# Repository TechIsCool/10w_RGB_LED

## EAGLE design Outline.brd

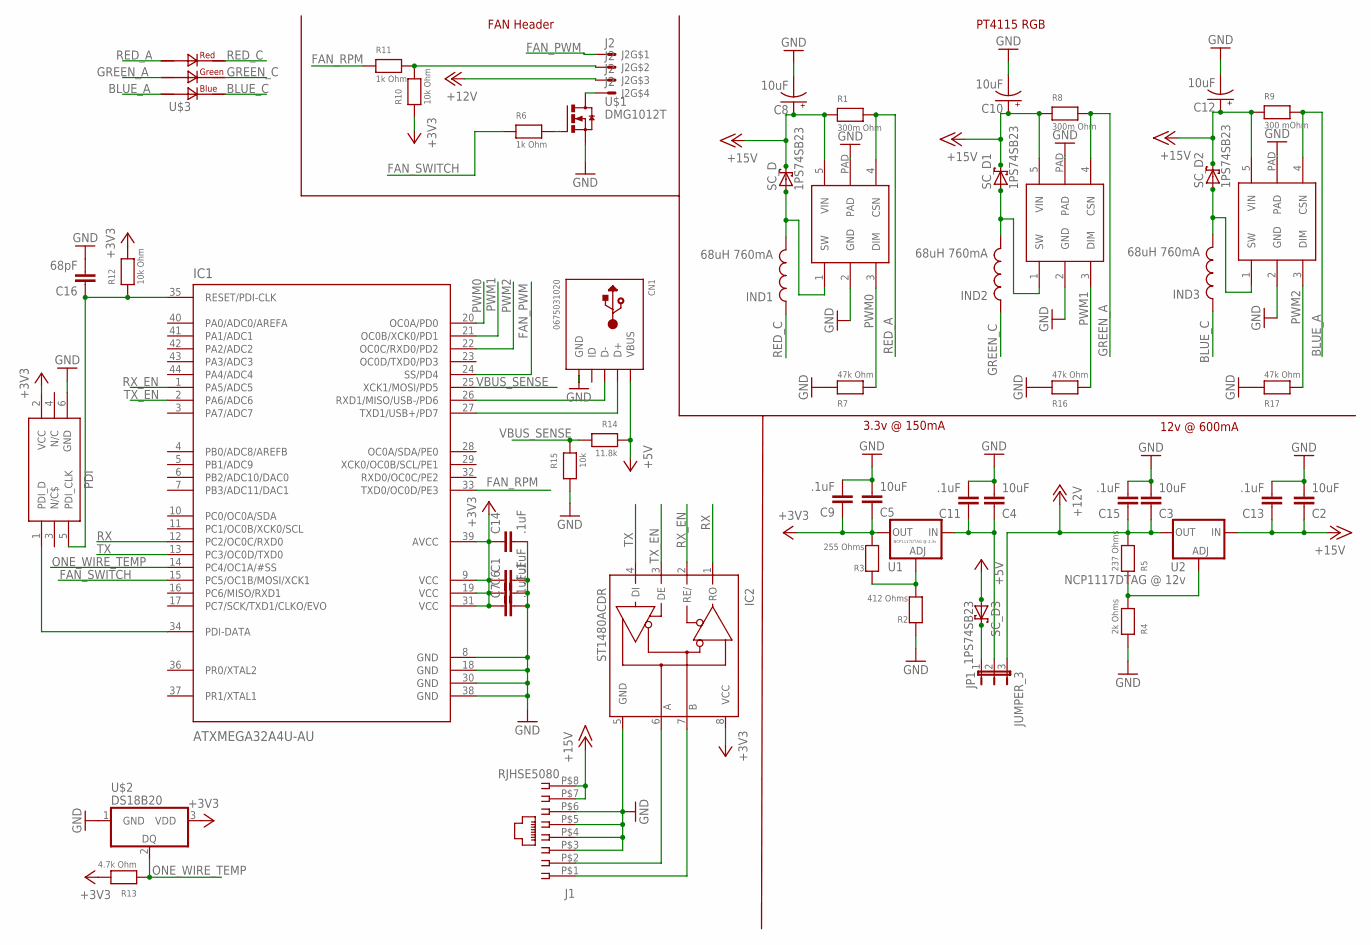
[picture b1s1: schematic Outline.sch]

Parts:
C1, C6, C7, C9, C11, C13, C14, C15: .1uF; 0603-CAP
C2, C3, C4, C5: 10uF; 1210
C8, C10, C12: 10uF; PANASONIC_C
C16: 68pF; 0603-CAP
CN1: 0675031020; MOLEX_675031020
DRV0, DRV1, DRV2: PT4115; SOT89-5
IC1: ATXMEGA32A4U-AU; TQFP-44
IC2: ST1480ACDR; SO08
IND1, IND2, IND3: 68uH 760mA; CR54
J1: RJHSE5080
J2: J2; 47053-1000
JP1: JUMPER_3; JP2E
PDI: AVR_PDI
R1, R8: 300m Ohm; 0805
R2: 412 Ohms; 0603
R3: 255 Ohms; 0603
R4: 2k Ohms; 0603
R5: 237 Ohms; 0603
R6, R11: 1k Ohm; 0603
R7, R16, R17: 47k Ohm; 0603
R9: 300 mOhm; 0805
R10, R12: 10k Ohm; 0603
R13: 4.7k Ohm; 0603
R14: 11.8k; 0603
R15: 10k; 0603
SC_D, SC_D1, SC_D2: 1PS74SB23; SOT-457
SC_D3: 1PS74SB23; NSR05F20
U1: NCP1117DTAG @ 3.3v; V-REG_DPACK
U2: NCP1117DTAG @ 12v; V-REG_DPACK
U$1: DMG1012T
U$2: DS18B20; TOP-92-INLINE
U$3: 10W_RGB_LED; 10W_LED

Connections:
+3V3: C1.1, C5.1, C6.1, C7.1, C9.1, C14.1, IC1.9 (VCC), IC1.19 (VCC), IC1.31 (VCC), IC1.39 (AVCC), IC2.8 (VCC), PDI.2 (VCC), R3.2, R10.1, R12.2, R13.2, U1.4 (OUT), U$2.3 (VDD)
+5V: CN1.P$1 (VBUS), R14.1, SC_D3.P$2 (A)
+12V: C3.1, C15.1, J2.3, JP1.3, R5.2, U2.4 (OUT)
+15V: C2.1, C8.+, C10.+, C12.+, C13.1, DRV0.5 (VIN), DRV1.5 (VIN), DRV2.5 (VIN), J1.P$7 (7), J1.P$8 (8), R1.1, R8.1, R9.1, SC_D.P$2 (C), SC_D.P$5 (C), SC_D1.P$2 (C), SC_D1.P$5 (C), SC_D2.P$2 (C), SC_D2.P$5 (C), U2.3 (IN)
BLUE_A: DRV2.4 (CSN), R9.2, U$3.B$A
BLUE_C: IND3.P$1 (1), U$3.B$C
FAN_PWM: IC1.24 (SS/PD4), J2.1
FAN_RPM: IC1.33 (TXD0/OC0D/PE3), R11.1
FAN_SWITCH: IC1.15 (PC5/OC1B/MOSI/XCK1), R6.1
GND: C1.2, C2.2, C3.2, C4.2, C5.2, C6.2, C7.2, C8.-, C9.2, C10.-, C11.2, C12.-, C13.2, C14.2, C15.2, C16.2, CN1.GND@1 (GND), CN1.GND@2 (GND), CN1.GND@3 (GND), CN1.GND@4 (GND), CN1.P$5 (GND), DRV0.2 (GND), DRV0.PAD, DRV1.2 (GND), DRV1.PAD, DRV2.2 (GND), DRV2.PAD, IC1.8 (GND), IC1.18 (GND), IC1.30 (GND), IC1.38 (GND), IC2.5 (GND), J1.P$3 (3), J1.P$4 (4), J1.P$5 (5), J1.P$6 (6), PDI.6 (GND), R2.1, R4.1, R7.1, R15.2, R16.1, R17.1, U$1.P$S (S), U$2.1 (GND)
GREEN_A: DRV1.4 (CSN), R8.2, U$3.G$A
GREEN_C: IND2.P$1 (1), U$3.G$C
unnamed: R2.2, R3.1, U1.1 (ADJ)
unnamed: R4.2, R5.1, U2.1 (ADJ)
unnamed: J2.4, U$1.P$D (D)
unnamed: R6.2, U$1.P$G (G)
unnamed: JP1.1, SC_D3.P$1 (C)
unnamed: DRV0.1 (SW), IND1.P$2 (2), SC_D.P$1 (A), SC_D.P$3 (A), SC_D.P$4 (A), SC_D.P$6 (A)
unnamed: DRV1.1 (SW), IND2.P$2 (2), SC_D1.P$1 (A), SC_D1.P$3 (A), SC_D1.P$4 (A), SC_D1.P$6 (A)
unnamed: DRV2.1 (SW), IND3.P$2 (2), SC_D2.P$1 (A), SC_D2.P$3 (A), SC_D2.P$4 (A), SC_D2.P$6 (A)
unnamed: IC1.34 (PDI-DATA), PDI.1 (PDI_D)
unnamed: C4.1, C11.1, JP1.2, U1.3 (IN)
unnamed: C16.1, IC1.35 (RESET/PDI-CLK), PDI.5 (PDI_CLK), R12.1
unnamed: J2.2, R10.2, R11.2
ONE_WIRE_TEMP: IC1.14 (PC4/OC1A/#SS), R13.1, U$2.2 (DQ)
PWM0: DRV0.3 (DIM), IC1.20 (OC0A/PD0), R7.2
PWM1: DRV1.3 (DIM), IC1.21 (OC0B/XCK0/PD1), R16.2
PWM2: DRV2.3 (DIM), IC1.22 (OC0C/RXD0/PD2), R17.2
RED_A: DRV0.4 (CSN), R1.2, U$3.R$A
RED_C: IND1.P$1 (1), U$3.R$C
RS485_N: IC2.7 (B), J1.P$1 (1)
RS485_P: IC2.6 (A), J1.P$2 (2)
RX: IC1.12 (PC2/OC0C/RXD0), IC2.1 (RO)
RX_EN: IC1.1 (PA5/ADC5), IC2.2 (RE/)
TX: IC1.13 (PC3/OC0D/TXD0), IC2.4 (DI)
TX_EN: IC1.2 (PA6/ADC6), IC2.3 (DE)
USB+: CN1.P$3 (D+), IC1.27 (TXD1/USB+/PD7)
USB-: CN1.P$2 (D-), IC1.26 (RXD1/MISO/USB-/PD6)
VBUS_SENSE: IC1.25 (XCK1/MOSI/PD5), R14.2, R15.1

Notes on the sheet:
3.3v @ 150mA
12v @ 600mA
PT4115 RGB
FAN Header

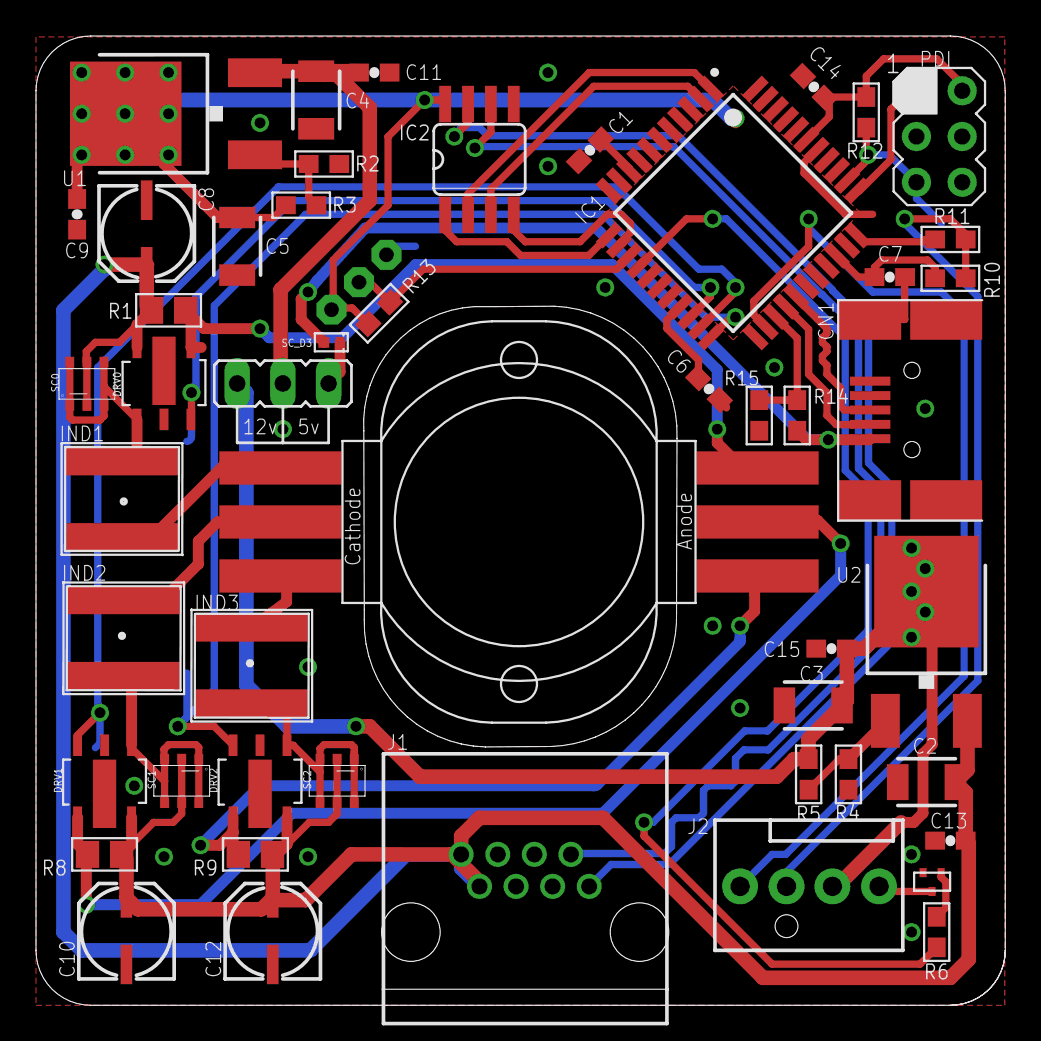
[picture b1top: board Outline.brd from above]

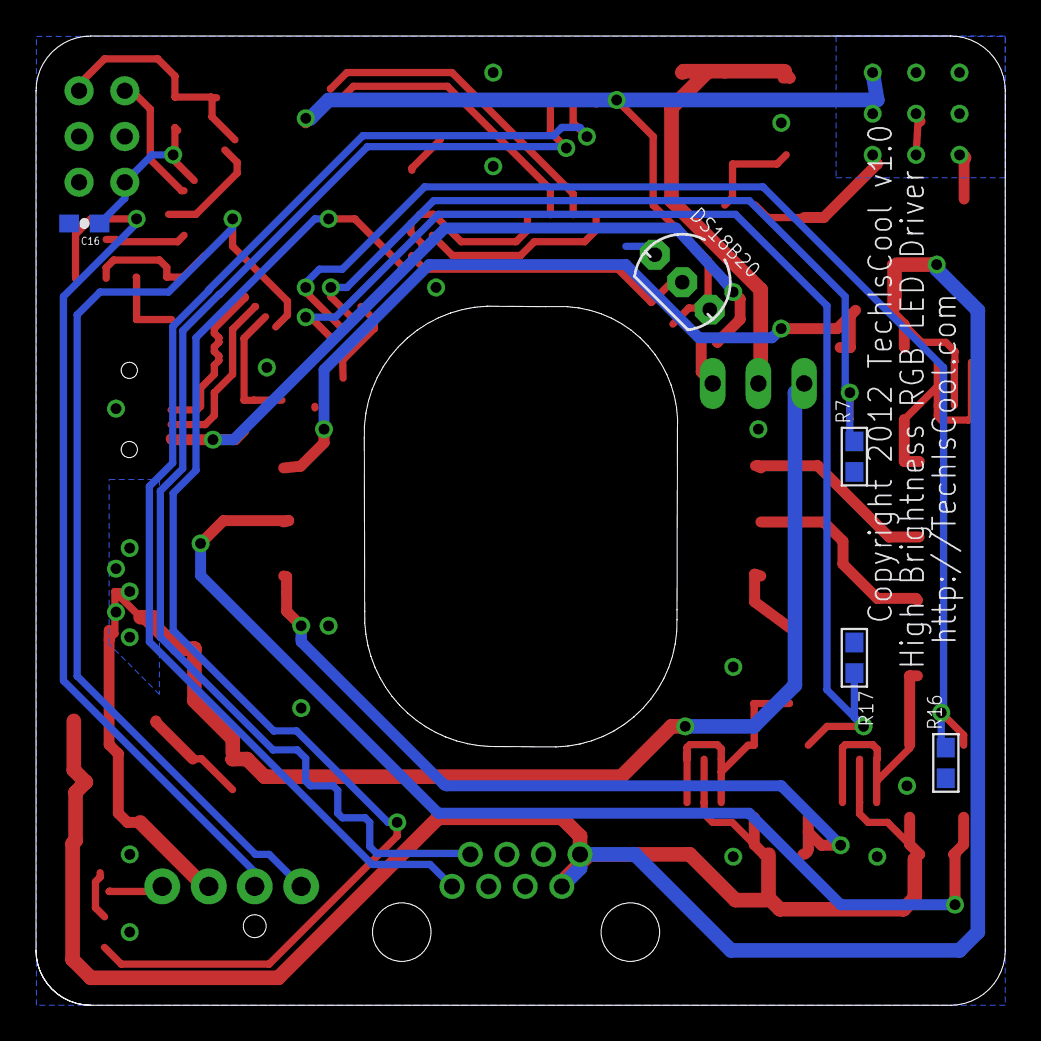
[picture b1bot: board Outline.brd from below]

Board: 2 copper layers, 53.8 x 53.8 mm, 55 parts (5 on the bottom side), 39 nets.

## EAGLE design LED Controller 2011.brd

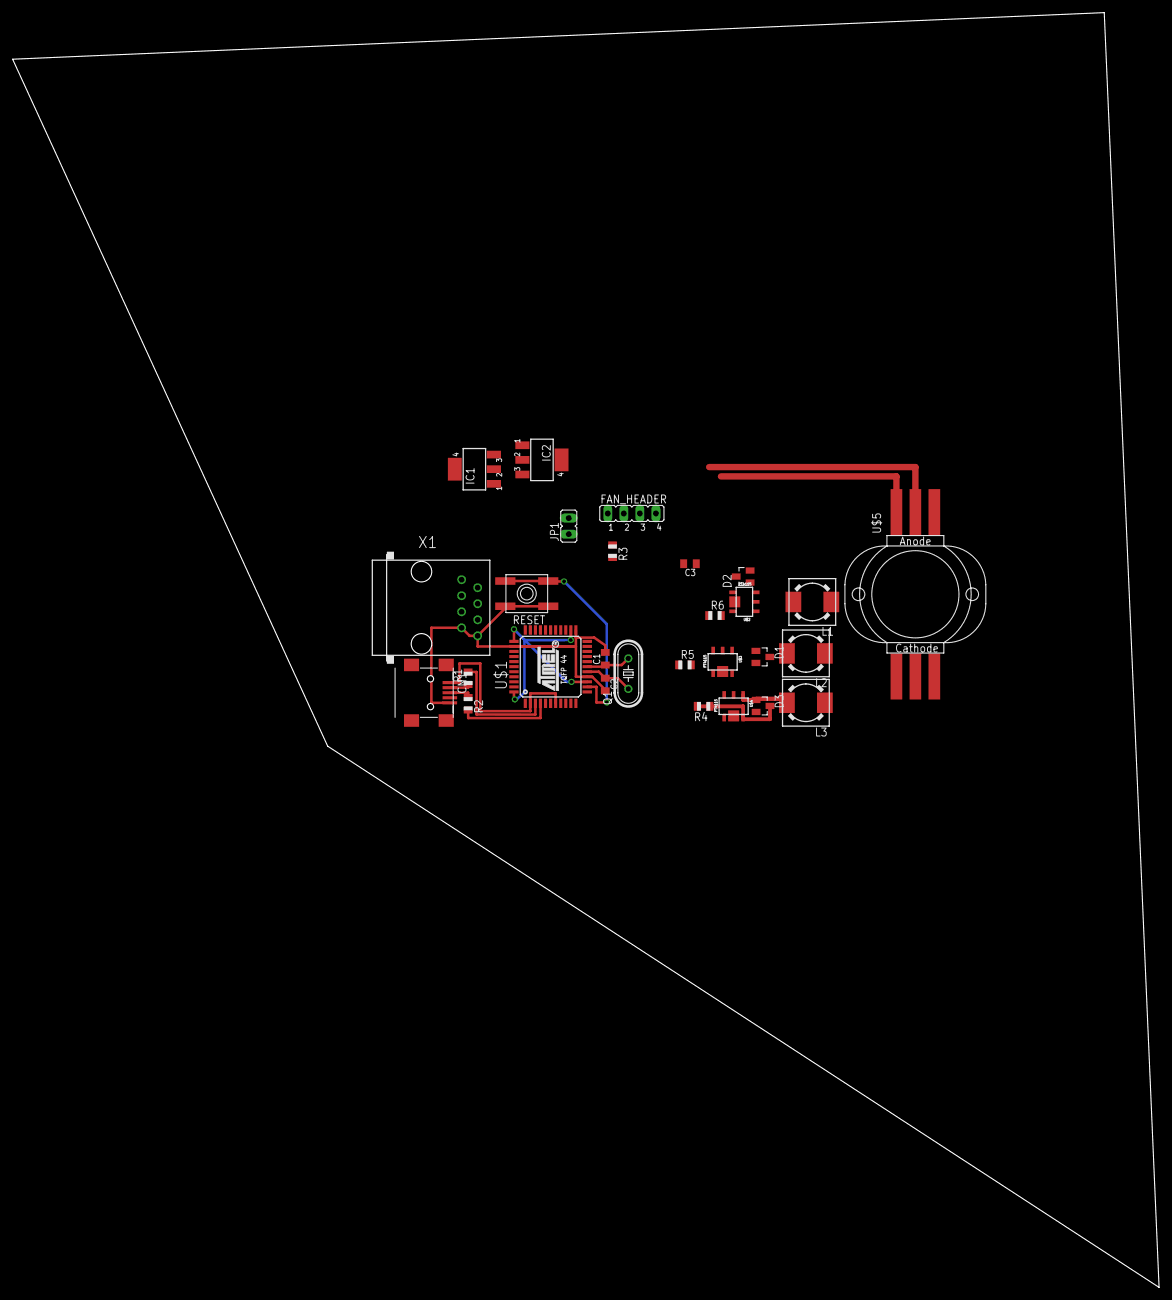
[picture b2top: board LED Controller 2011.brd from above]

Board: 2 copper layers, 181.4 x 201.7 mm, 28 parts (0 on the bottom side), 25 nets.

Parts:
C1, C2, C3: 18pF; C0805K
CN1: USB-MINIB
D1, D2, D3: BAS40; SOT23
FAN_HEADER: JP4
IC1, IC2: MCP1703DB; SOT223
JP1: HWB; JP1
L1, L2, L3: DR74
Q1: 16Mhz; HC49/S
R1, R2: 22; R0805
R3: 10K; R0805
R4, R5, R6: .13Ohm; R0805
RESET: EVQQ2; EVQ-Q2
U$1: ATMEGA32U4-AU; TQFP44
U$2, U$3, U$4: PT4115; SOT89-5
U$5: 10W_RGB_LED
X1: RJ45-6X; RJ45-NO-SHIELD

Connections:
+5V: CN1.VBUS, IC1.3, U$1.2, U$1.7
+12V: FAN_HEADER.2, IC2.3
+15V: D1.3, D2.3, D3.3, IC1.1, IC2.1, R4.2, R5.2, R6.2, U$2.5, U$3.5, U$4.5, X1.4, X1.5
DIM_BLUE: U$1.12, U$4.3
DIM_GREEN: U$1.30, U$3.3
DIM_RED: U$1.29, U$2.3
GND: C1.2, C2.2, C3.2, CN1.GND, IC1.2, IC2.2, JP1.2, RESET.B, RESET.B', U$1.15, U$1.23, U$1.35, U$1.43, U$2.2, U$3.2, U$4.2, X1.7, X1.8
HWB: JP1.1, R3.1, U$1.33
unnamed: CN1.D-, R1.1
unnamed: R2.2, U$1.4
unnamed: R1.2, U$1.3
unnamed: CN1.D+, R2.1
unnamed: C1.1, Q1.2, U$1.17
unnamed: RESET.A, RESET.A', U$1.13
unnamed: C2.1, Q1.1, U$1.16
unnamed: R4.1, U$2.4, U$5.R$2
unnamed: L1.1, U$5.R$1
unnamed: L2.1, U$5.G$1
unnamed: R5.1, U$3.4, U$5.G$2
unnamed: L3.1, U$5.B$1
unnamed: R6.1, U$4.4, U$5.B$2
unnamed: D3.1, L3.2, U$4.1
unnamed: D1.1, L2.2, U$3.1
unnamed: D2.1, L1.2, U$2.1
VCC: R3.2, U$1.14, U$1.24, U$1.34, U$1.44

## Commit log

2012-12-18 2011 Commit
2012-12-18 2012 Commit
2012-12-18 Version 2
2012-12-18 Version 3
2012-12-18 Version 4
2012-12-18 Version 4.1
2012-12-19 Cleaned Up some
    Still have a trace broken though
2012-12-19 Still have an airwire
    Not sure why
2012-12-19 Version 4.1a
    Found the issue
2012-12-20 4.1b
    Updated and removed files
2012-12-20 4.1c
2012-12-20 4.1d
2012-12-20 4.2
    Rounded Corners with some final touch up.
2012-12-22 4.2.1
    Updated Layout
2012-12-22 4.2.2
    Connected a few things and add a via. Also gnded the extra wires in the
    RJ45 cable
2012-12-22 4.2.3
    Aligned the via's
2012-12-25 4.2.4
    Final Version Submitted aka v1.0
2013-05-03 4.3
    Changed LDO resistor values to stop overheating. Added 68pf cap between
    reset and ground to make AVR Dragon talk with device.

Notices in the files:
Outline.brd:
Copyright 2012 TechIsCool v1.0
parts and their libraries:
SparkFun: Licensing: CC v3.0 Share-Alike You are welcome to use this library for commercial purposes.
